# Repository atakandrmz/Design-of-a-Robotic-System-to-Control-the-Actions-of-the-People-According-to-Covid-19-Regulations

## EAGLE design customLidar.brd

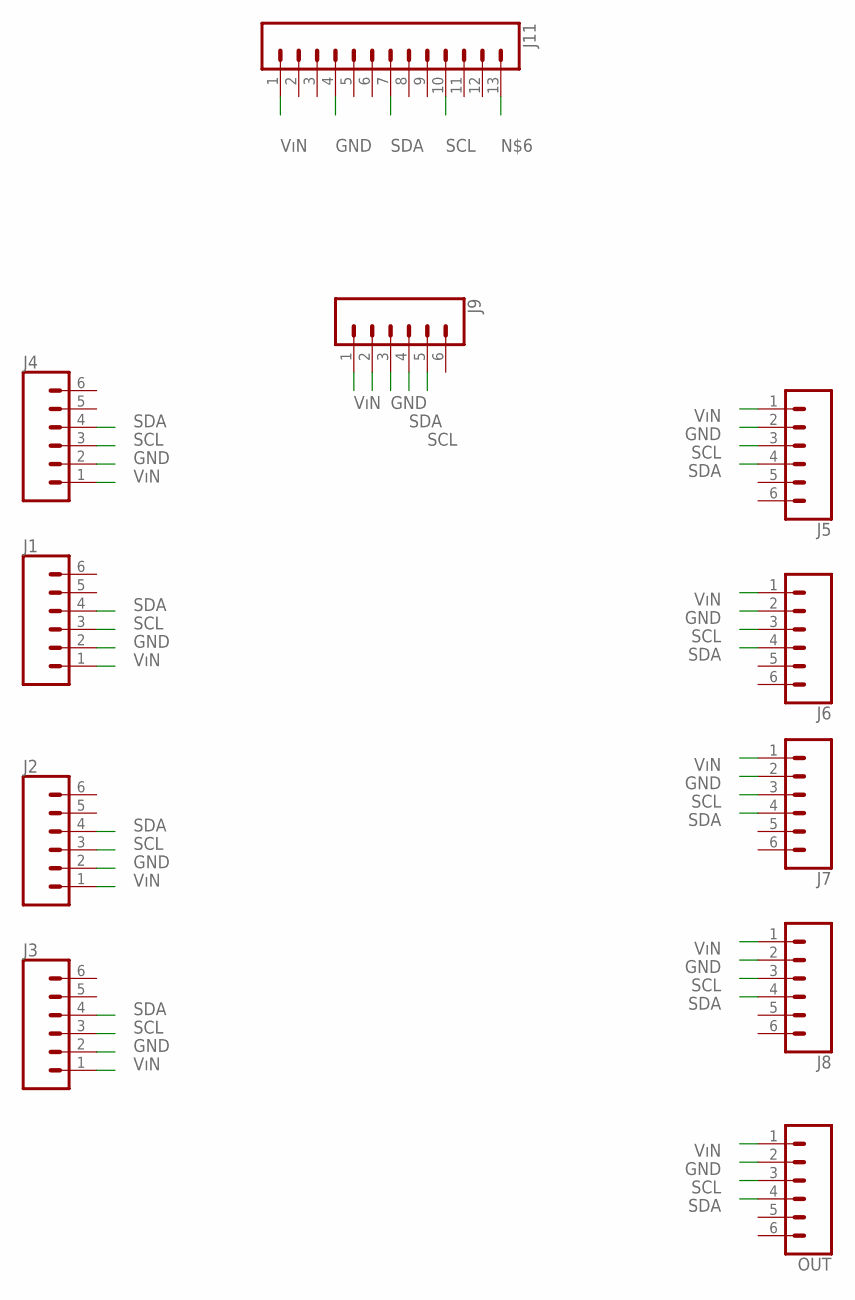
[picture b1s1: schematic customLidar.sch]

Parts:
J1, J2, J3, J4, J5, J6, J7, J8, J9: CONN_06LONGPADS; 1X06_LONGPADS
J11: CONN_13LONGPADS; 1X13-LONGPADS
OUT: CONN_06LONGPADS; 1X06_LONGPADS

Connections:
GND: J1.2, J2.2, J3.2, J4.2, J5.2, J6.2, J7.2, J8.2, J9.3, J11.4, OUT.2
SCL: J1.3, J2.3, J3.3, J4.3, J5.3, J6.3, J7.3, J8.3, J9.5, J11.10, OUT.3
SDA: J1.4, J2.4, J3.4, J4.4, J5.4, J6.4, J7.4, J8.4, J9.4, J11.7, OUT.4
VıN: J1.1, J2.1, J3.1, J4.1, J5.1, J6.1, J7.1, J8.1, J9.1, J11.1, OUT.1

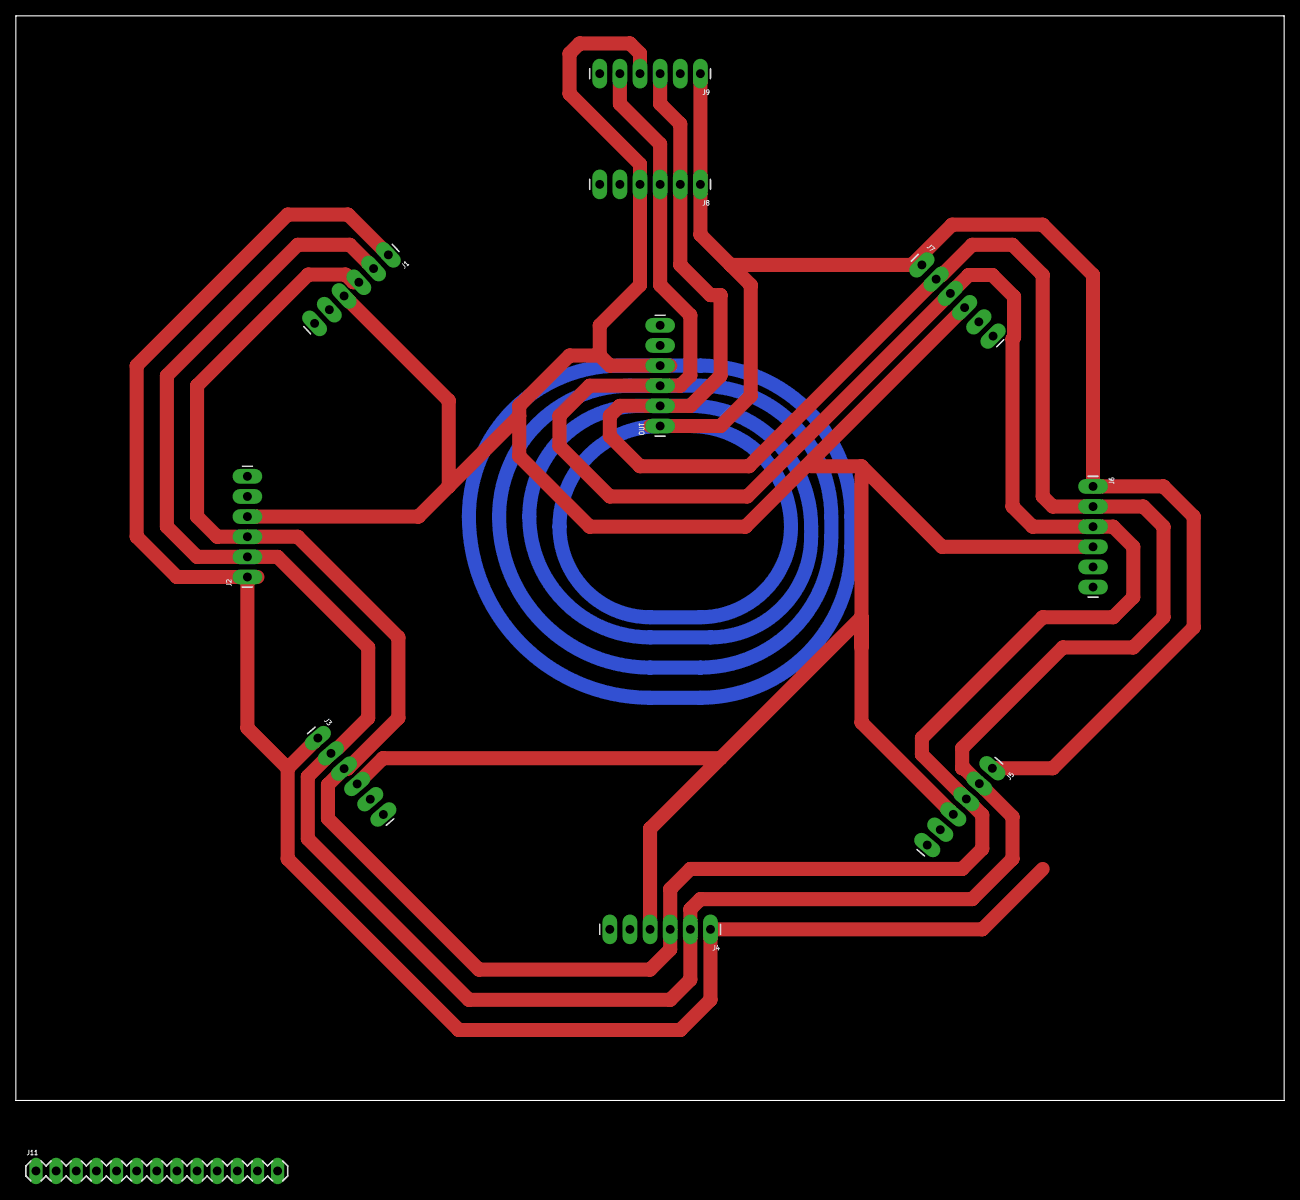
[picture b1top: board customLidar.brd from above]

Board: 2 copper layers, 160.0 x 136.8 mm, 11 parts (0 on the bottom side), 4 nets.

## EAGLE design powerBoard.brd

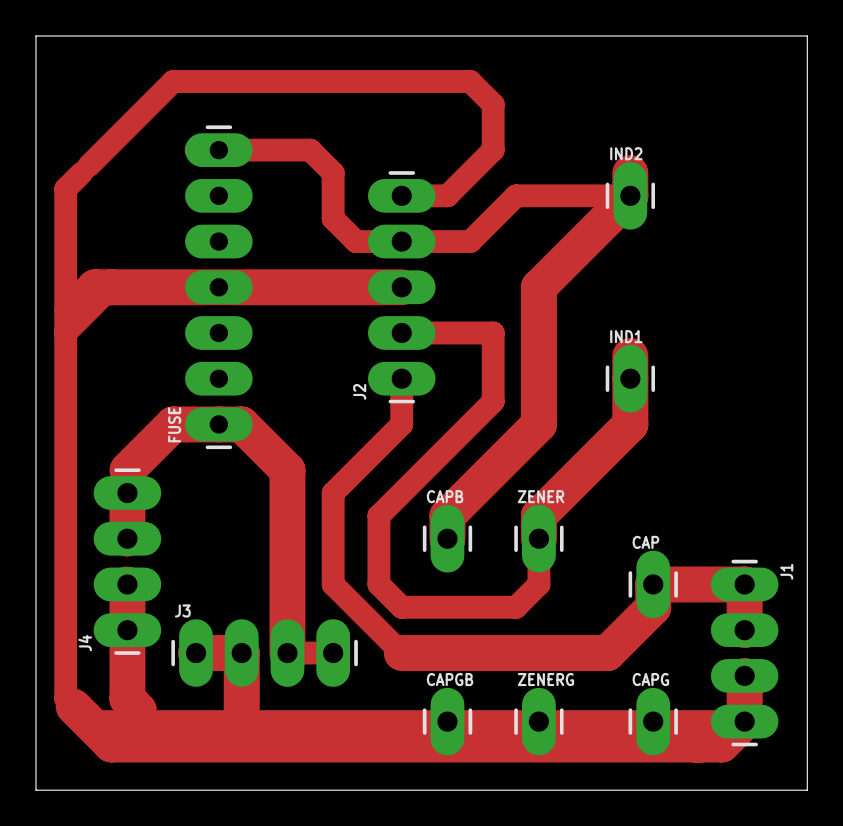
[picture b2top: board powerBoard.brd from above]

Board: 2 copper layers, 42.9 x 41.9 mm, 13 parts (0 on the bottom side), 6 nets.

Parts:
CAP: 1X01_LONGPAD
CAPB: 1X01_LONGPAD
CAPG: 1X01_LONGPAD
CAPGB: 1X01_LONGPAD
FUSE: 1X07_LONGPADS
IND1, IND2: 1X01_LONGPAD
J1, J3, J4: 1X04_LONGPADS
J2: 1X05_LONGPADS
ZENER: 1X01_LONGPAD
ZENERG: 1X01_LONGPAD

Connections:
GND: CAPG.1, CAPGB.1, FUSE.4, J2.3, J2.5, J3.1, J3.2, J4.1, J4.2, ZENERG.1
INPUT: CAP.1, J1.1, J1.2, J2.1
unnamed: CAPB.1, FUSE.7, IND2.1, J2.4
unnamed: IND1.1, J2.2, ZENER.1
unnamed: J1.3, J1.4
OUTPUT: FUSE.1, J3.3, J3.4, J4.3, J4.4

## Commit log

2021-07-11 Face and Eye Detection Code
2021-07-11 Circuit Design for the Power Board
2021-07-11 Low Cost LIDAR Design
2021-07-11 Add files via upload
    Design of a Robotic System to Control the Actions of the People According to Covid-19 Regulations in a Highly Populated Indoor Area

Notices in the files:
parts and their libraries:
SparkFun-Connectors: Licensing: Creative Commons ShareAlike 4.0 International - https://creativecommons.org/licenses/by-sa/4.0
